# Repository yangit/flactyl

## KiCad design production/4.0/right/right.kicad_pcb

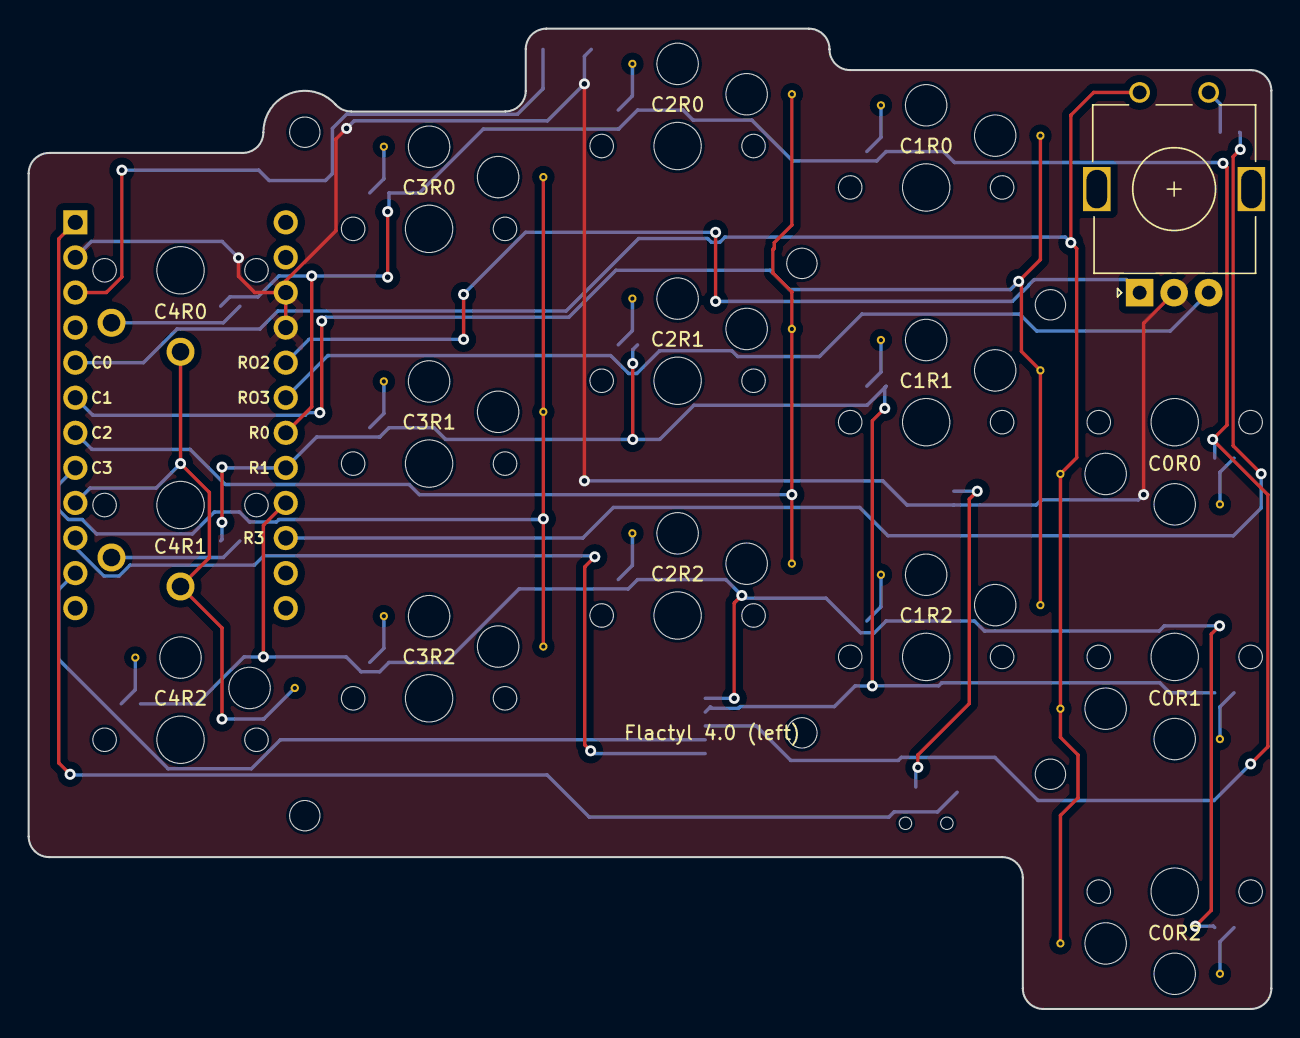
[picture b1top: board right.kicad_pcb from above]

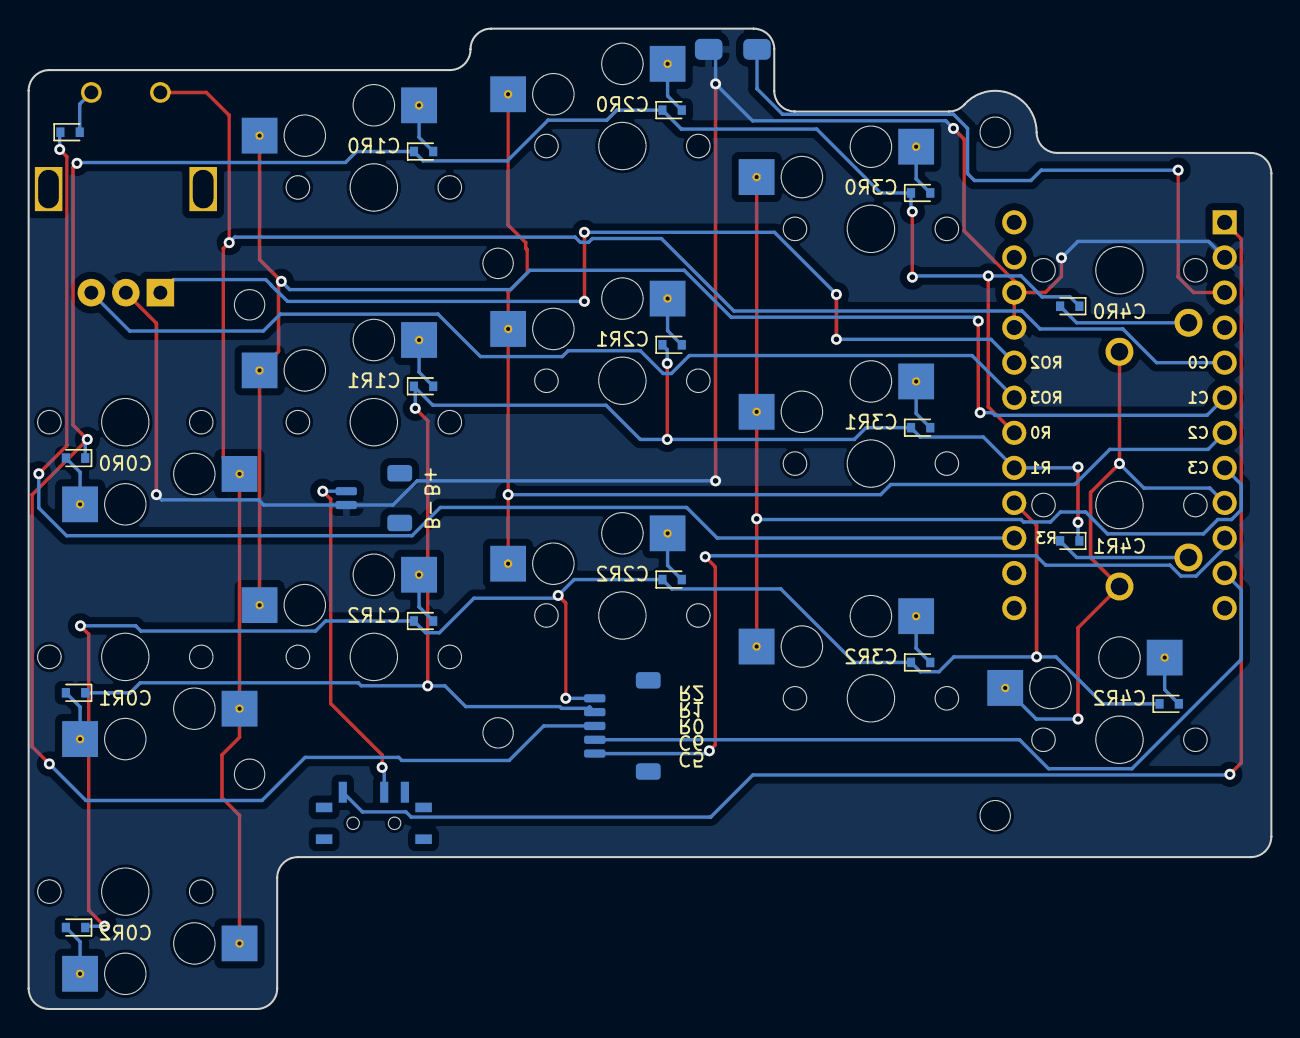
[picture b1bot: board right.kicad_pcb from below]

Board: 2 copper layers, 90.0 x 71.0 mm, 44 parts (35 on the bottom side), 33 nets.

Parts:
D1, D2, D3, D4, D5, D6, D7, D8, D9, D10, D11, D12, D13, D14, D15, D16: D_SOD-523
H1, H2, H3, H4, H5, H6: MountingHole_2.2mm_M2
JB1: JST_SH_SM02B-SRSS-TB_1x02-1MP_P1.00mm_Horizontal
JC1: JST_SH_SM05B-SRSS-TB_1x05-1MP_P1.00mm_Horizontal
MCU1: NiceNano
ROT1: rotary_encoder
S1, S2, S3, S4, S5, S6, S7, S8, S9, S10, S11, S12, S13, S14, S15: Kailh_socket_PG1350_no_silk
SB1: b3u-1000P
SS1: SW-TH_MSK12C02-HB-1
T1: Flactyl 4.0 (left); somelogo

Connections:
BSLI: JB1.2, SS1.2
C0: MCU1.5, ROT1.1, S1.2, S1.4, S2.2, S2.4, S3.2, S3.4
C0R0D: D1.2, S1.1, S1.3
C0R1D: D2.2, S2.1, S2.3
C0R2D: D3.2, S3.1, S3.3
C0R3D: D16.2, ROT1.2
C1: MCU1.6, S4.2, S4.4, S5.2, S5.4, S6.2, S6.4
C1R0D: D4.2, S4.1, S4.3
C1R1D: D5.2, S5.1, S5.3
C1R2D: D6.2, S6.1, S6.3
C2: MCU1.7, S7.2, S7.4, S8.2, S8.4, S9.2, S9.4
C2R0D: D7.2, S7.1, S7.3
C2R1D: D8.2, S8.1, S8.3
C2R2D: D9.2, S9.1, S9.3
C3: MCU1.8, S10.2, S10.4, S11.2, S11.4, S12.2, S12.4
C3R0D: D10.2, S10.1, S10.3
C3R1D: D11.2, S11.1, S11.3
C3R2D: D12.2, S12.1, S12.3
C4: MCU1.9, S13.2, S14.2, S15.2, S15.4
C4R0D: D13.2, S13.1
C4R1D: D14.2, S14.1
C4R2D: D15.2, S15.1, S15.3
C5: JC1.1, MCU1.10
C6: JC1.2, MCU1.11
GND: JB1.1, MCU1.2, MCU1.15, MCU1.16, ROT1.C, SB1.1
P2: MCU1.17, ROT1.A
P3: MCU1.18, ROT1.B
R0: D1.1, D4.1, D7.1, D10.1, D13.1, JC1.3, MCU1.19
R1: D2.1, D5.1, D8.1, D11.1, D14.1, JC1.4, MCU1.20
R2: D3.1, D6.1, D9.1, D12.1, D15.1, JC1.5, MCU1.21
R3: D16.1, MCU1.22
RAW: MCU1.1, SS1.1
RST: MCU1.3, SB1.2

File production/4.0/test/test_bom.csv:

Comment,Designator,Footprint,LCSC
"DIODE","D1,D2","Yan:D_SOD-523","C511874"
"JC","JC1","Yan:JST_SH_SM05B-SRSS-TB_1x05-1MP_P1.00mm_Horizontal","C136657"
"JB","JB1","Yan:JST_SH_SM02B-SRSS-TB_1x02-1MP_P1.00mm_Horizontal","C160402"
"SB","SB1","Yan:b3u-1000P","C231329"
"SS","SS1","Yan:Side switch","C431541"

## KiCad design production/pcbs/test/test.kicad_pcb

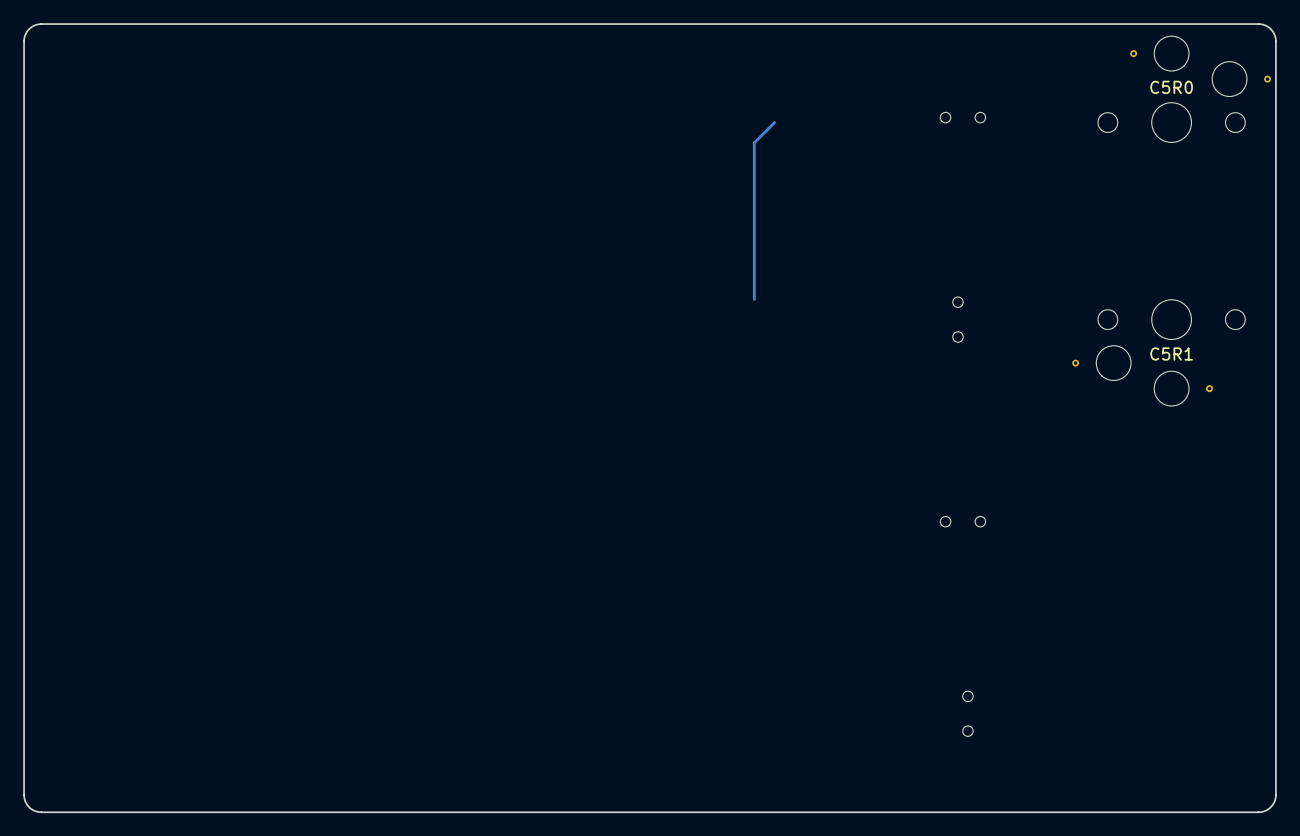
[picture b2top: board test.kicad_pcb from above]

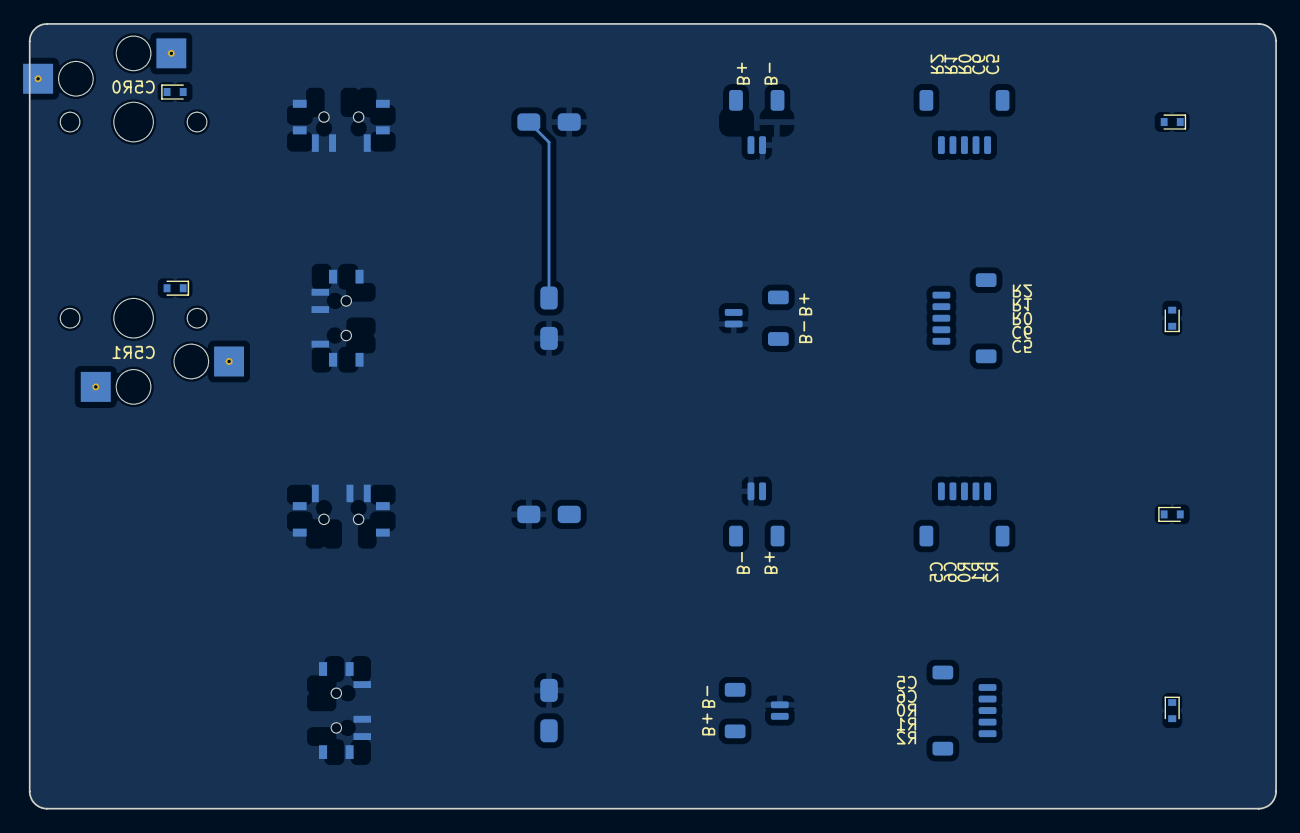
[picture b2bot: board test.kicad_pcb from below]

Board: 2 copper layers, 108.0 x 68.0 mm, 26 parts (20 on the bottom side), 14 nets.

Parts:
D1, D2, D3, D4, D5, D6: D_SOD-523
JB1, JB2, JB3, JB4: JST_SH_SM02B-SRSS-TB_1x02-1MP_P1.00mm_Horizontal
JC1, JC2, JC3, JC4: JST_SH_SM05B-SRSS-TB_1x05-1MP_P1.00mm_Horizontal
S1, S2: Kailh_socket_PG1350_no_silk
SB1, SB2, SB3, SB4: b3u-1000P
SS1, SS2, SS3, SS4: SW-TH_MSK12C02-HB-1
T1: x; somelogo
T2: y; somelogo

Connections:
BSLI: JB1.2, JB2.2, JB3.2, JB4.2, SS1.2, SS2.2, SS3.2, SS4.2
C5: JC1.1, JC2.1, JC3.1, JC4.1, S1.2, S1.4, S2.2, S2.4
C5R0D: D5.2, S1.1, S1.3
C5R1D: D6.2, S2.1, S2.3
C6: JC1.2, JC2.2, JC3.2, JC4.2
GND: JB1.1, JB2.1, JB3.1, JB4.1, SB1.1, SB2.1, SB3.1, SB4.1
R0: D5.1, JC1.3, JC2.3, JC3.3, JC4.3
R1: D6.1, JC1.4, JC2.4, JC3.4, JC4.4
R2: JC1.5, JC2.5, JC3.5, JC4.5
RAW: SS1.1, SS2.1, SS3.1, SS4.1
RST: SB1.2, SB2.2, SB3.2, SB4.2
f: D1.2, D2.2, D3.2, D4.2
t: D1.1, D2.1, D3.1, D4.1
three: SS1.3, SS2.3, SS3.3
